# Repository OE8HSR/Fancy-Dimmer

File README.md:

# Fancy-Dimmer
The Fancy-Dimmer is "designed" to dim LED Flatpanels.\
(Flatpanels are used to make CallibrationFrames in Astrophotography)\
**Input:** 12Vdc (10V-14,4V)\
**Output:** 12V PWM\
**PWM-Frequency:** 30kHz (Programable)\
**Imax:** 5A\
**PWM-Resolution:** 668 Counts\
Potentiometer controlled\
2 x "programable" Presets\
Programable via UPDI\
\

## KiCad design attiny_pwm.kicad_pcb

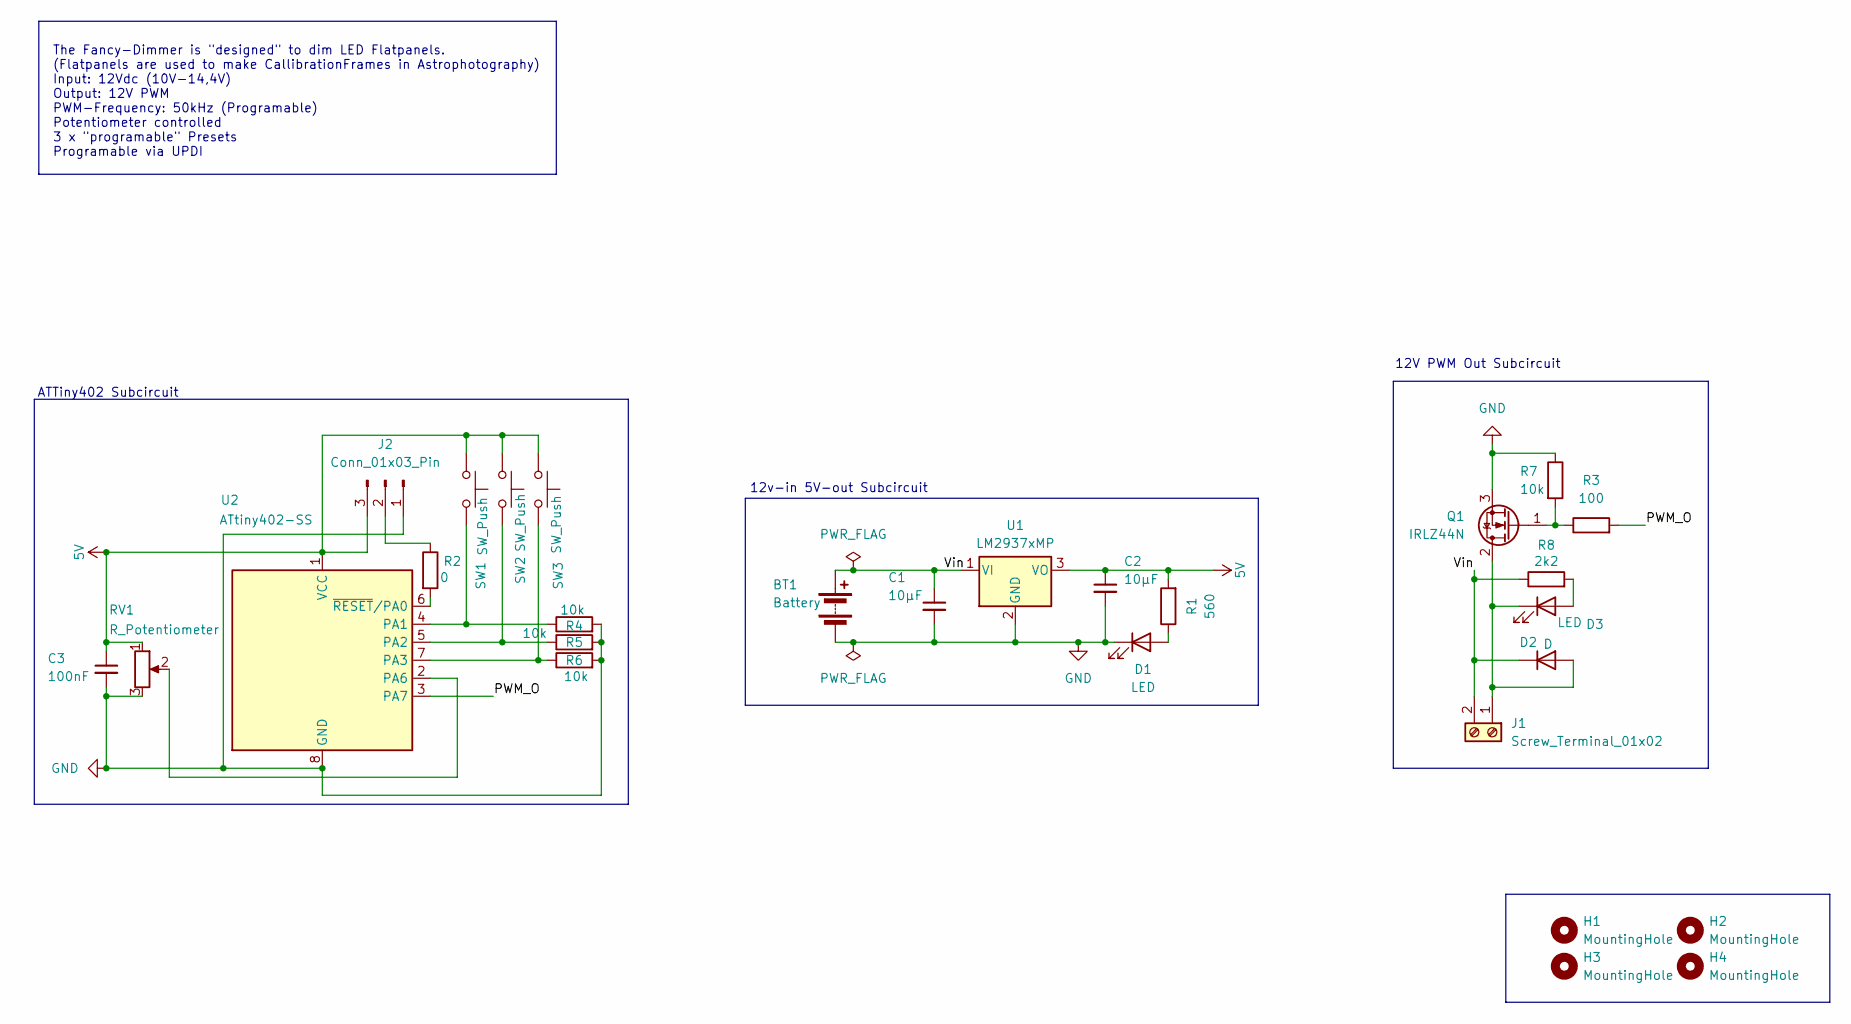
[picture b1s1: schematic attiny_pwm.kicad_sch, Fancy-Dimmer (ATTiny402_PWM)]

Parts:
BT1: Battery; TerminalBlock_MaiXu_MX126-5.0-02P_1x02_P5.00mm
C1, C2: 10µF; C_0805_2012Metric; Voltage 1kV; Tolerance 100%
C3: 100nF; C_0603_1608Metric; Voltage 1kV; Tolerance 100%
D1, D3: LED; LED_0805_2012Metric
D2: D; D_0603_1608Metric
H1, H2, H3, H4: MountingHole; MountingHole_3.2mm_M3_DIN965
J1: Screw_Terminal_01x02; TerminalBlock_MaiXu_MX126-5.0-02P_1x02_P5.00mm
J2: Conn_01x03_Pin; PinHeader_1x03_P2.54mm_Vertical
Q1: IRLZ44N; TO-263-3_TabPin2
R1: 560; R_0805_2012Metric
R2: 0; R_0805_2012Metric
R3: 100; R_0805_2012Metric
R4, R5, R6, R7: 10k; R_0805_2012Metric
R8: 2k2; R_0805_2012Metric
RV1: R_Potentiometer; TerminalBlock_MaiXu_MX126-5.0-03P_1x03_P5.00mm
SW1, SW2, SW3: SW_Push; SW_SPST_B3SL-1002P
U1: LM2937xMP; TO-263-3_TabPin4
U2: ATtiny402-SS; SOIC-8_3.9x4.9mm_P1.27mm

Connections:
5V: C2.1, C3.1, J2.3, R1.2, RV1.1, SW1.1, SW2.1, SW3.1, U1.3 (VO), U2.1 (VCC)
/PWM_O: R3.2, U2.3 (PA7)
/Vin: BT1.1 (+), C1.1, D2.1 (K), J1.2, R8.1, U1.1 (VI)
GND: BT1.2 (-), C1.2, C2.2, C3.2, D1.1 (K), J2.1, Q1.3 (S), R4.2, R5.2, R6.2, R7.1, RV1.3, U1.2 (GND), U2.8 (GND)
unnamed: D1.2 (A), R1.1
unnamed: D2.2 (A), D3.1 (K), J1.1, Q1.2 (D)
unnamed: D3.2 (A), R8.2
unnamed: J2.2, R2.1
unnamed: Q1.1 (G), R3.1, R7.2
unnamed: R4.1, SW1.2, U2.4 (PA1)
unnamed: R5.1, SW2.2, U2.5 (PA2)
unnamed: R6.1, SW3.2, U2.7 (PA3)
unnamed: RV1.2, U2.2 (PA6)
unnamed: R2.2, U2.6 (~RESET/PA0)

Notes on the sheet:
12V PWM Out Subcircuit
12v-in 5V-out Subcircuit
ATTiny402 Subcircuit
The Fancy-Dimmer is "designed" to dim LED Flatpanels. (Flatpanels are used to make CallibrationFrames in Astrophotography) Input: 12Vdc (10V-14,4V) Output: 12V PWM PWM-Frequency: 50kHz (Programable) Potentiometer controlled 3 x "programable" Presets Programable via UPDI

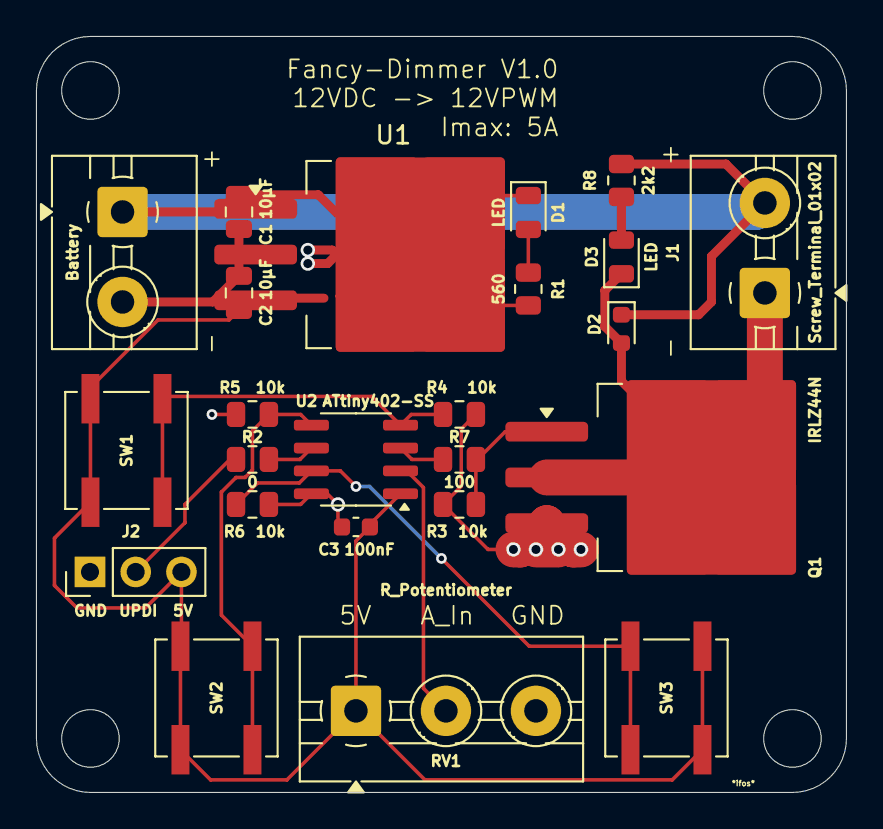
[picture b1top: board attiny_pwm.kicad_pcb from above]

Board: 2 copper layers, 45.0 x 42.0 mm, 28 parts (0 on the bottom side), 14 nets.

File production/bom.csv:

Designator,Footprint,Quantity,Value,LCSC Part #
BT1,TerminalBlock_MaiXu_MX126-5.0-02P_1x02_P5.00mm,1,Battery,
"C1, C2",0805,2,10µF,
C3,0603,1,100nF,
"D1, D3",0805,2,LED,
D2,0603,1,D,
J1,TerminalBlock_MaiXu_MX126-5.0-02P_1x02_P5.00mm,1,Screw_Terminal_01x02,
J2,PinHeader_1x03_P2.54mm_Vertical,1,Conn_01x03_Pin,
Q1,TO-263-3_TabPin2,1,IRLZ44N,
R1,0805,1,560,
R2,0805,1,0,
R3,0805,1,100,
"R4, R5, R6, R7",0805,4,10k,
R8,0805,1,2k2,
RV1,TerminalBlock_MaiXu_MX126-5.0-03P_1x03_P5.00mm,1,R_Potentiometer,
"SW1, SW2, SW3",SW_SPST_B3SL-1002P,3,SW_Push,
U1,TO-263-3_TabPin4,1,LM2937xMP,
U2,SOIC-8_3.9x4.9mm_P1.27mm,1,ATtiny402-SS,

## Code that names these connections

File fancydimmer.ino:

/*
 * Firmware for FancyDimmer
 */

#include <EEPROM.h>

const uint8_t EEPROM_MARKER_B2 = 0xA5;
const uint8_t EEPROM_MARKER_B3 = 0x5A;
const uint8_t EEPROM_ADDR_B2   = 0;
const uint8_t EEPROM_ADDR_B3   = 4;



uint32_t lastButton1Time = 0;
uint8_t  button1ClickCount = 0;
bool lastB1State = false;
bool ispressed = false;
uint16_t value = 0;
uint16_t pwmWert = 0;
int pwmold = 0;
int poti = 0;
int newpwm = 0;
int oldpwm = 0;
uint16_t smoothed = 0;



const uint16_t PWM_TOP = 668;//30khz
const uint8_t button1 = PIN_PA1;
const uint8_t button2 = PIN_PA2;
const uint8_t button3 = PIN_PA3;

void blinkPWM(uint8_t times, uint16_t del) {
  for (uint8_t i = 0; i < times; i++) {
    TCA0.SINGLE.CMP0 = 0;         // LED aus
    delay(del);
    TCA0.SINGLE.CMP0 = PWM_TOP;  // LED an
    delay(del);
  }
}

void writePWMtoEEPROM(uint8_t slotAddr, uint8_t marker, uint16_t value) {
  EEPROM.update(slotAddr, marker);
  EEPROM.update(slotAddr + 1, value >> 8);
  EEPROM.update(slotAddr + 2, value & 0xFF);
}

bool readPWMfromEEPROM(uint8_t slotAddr, uint8_t marker, uint16_t &valueOut) {

    uint8_t high = EEPROM.read(slotAddr + 1);
    uint8_t low  = EEPROM.read(slotAddr + 2);
    valueOut = ((uint16_t)high << 8) | low;

}

void clearEEPROM() {
  for (uint8_t i = 0; i < 6; i++) EEPROM.update(i, 0xFF);
}



void setup() {
TCA0.SINGLE.CMP0 = 0;

  pinMode(button1, INPUT);
  pinMode(button2, INPUT);
  pinMode(button3, INPUT);

  TCA0.SPLIT.CTRLA = 0;

  PORTA.DIRSET = PIN7_bm;

  TCA0.SINGLE.CTRLA = 0;
  TCA0.SPLIT.CTRLA  = 0;
  TCA0.SPLIT.CTRLB  = 0;
  TCA0.SINGLE.CNT   = 0;
  TCA0.SPLIT.CTRLD  = 0;
  TCA0.SINGLE.CTRLB = TCA_SINGLE_WGMODE_SINGLESLOPE_gc | TCA_SINGLE_CMP0EN_bm;
  TCA0.SINGLE.PER = PWM_TOP;
  TCA0.SINGLE.CMP0 = 0;
  TCA0.SINGLE.CTRLA = TCA_SINGLE_CLKSEL_DIV1_gc | TCA_SINGLE_ENABLE_bm;
}

void loop() {


int raw = ((uint32_t)analogRead(PIN_PA6) * PWM_TOP) / 1023;
bool b1 = digitalRead(button1);
bool b2 = digitalRead(button2);
bool b3 = digitalRead(button3);

if((abs(oldpwm - raw)) > 2){
  pwmWert = PWM_TOP - raw;
  oldpwm = raw; 
}
else {
  pwmWert = PWM_TOP - oldpwm ;
}





if (b1 && !lastB1State) {
  uint32_t now = millis();
  if (now - lastButton1Time < 2000) {
    button1ClickCount++;
  } else {
    button1ClickCount = 1;
  }
  lastButton1Time = now;

  if (button1ClickCount >= 5) {
    clearEEPROM(); 
    delay(500);
    blinkPWM(5, 500); 
    button1ClickCount = 0;
  }
}
lastB1State = b1;

if(b2 && b1) {
  writePWMtoEEPROM(EEPROM_ADDR_B2, EEPROM_MARKER_B2, pwmWert);
  blinkPWM(2, 1000);
}
else if(b3 && b1) {
  writePWMtoEEPROM(EEPROM_ADDR_B3, EEPROM_MARKER_B3, pwmWert);
  blinkPWM(2, 1000);
  
}
else if(b2) {
  readPWMfromEEPROM(EEPROM_ADDR_B2, EEPROM_MARKER_B2, value);
  pwmold = pwmWert;
  ispressed = true;
  blinkPWM(3, 100);
  
}
else if(b3) {
  readPWMfromEEPROM(EEPROM_ADDR_B3, EEPROM_MARKER_B3, value);
  pwmold = pwmWert;
  ispressed = true;
  blinkPWM(3, 100);
  
}


if(ispressed) {
  TCA0.SINGLE.CMP0 = value;
  if(abs(pwmold - pwmWert) >= 3){
    ispressed = false;
    pwmold = pwmWert;
  }
  return;
}

TCA0.SINGLE.CMP0 = pwmWert;

}

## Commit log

2025-03-27 Files Uploaded
2025-03-27 Update README.md
    updated readme
2025-03-27 uploaded BOM
2025-03-27 Update README.md
    updated readmy
2025-04-08 erased fuckups
2025-04-08 uploaded html BOM and production files
2025-04-21 uploaded housing files and firmware
